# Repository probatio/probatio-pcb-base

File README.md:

# PCB for Support
A support is a part of probatio for expanding possible user's postures.

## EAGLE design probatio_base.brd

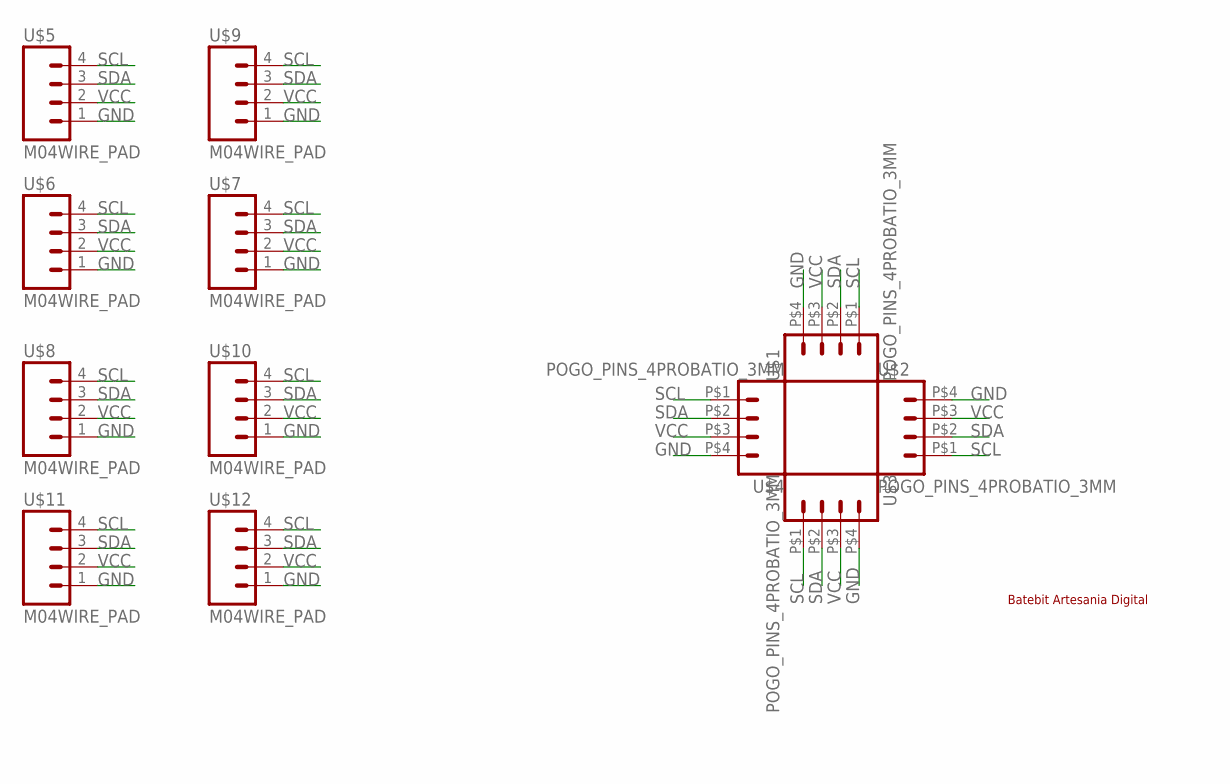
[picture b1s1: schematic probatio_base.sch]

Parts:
U$1, U$2, U$3, U$4: POGO_PINS_4PROBATIO_3MM; POGO-PINS-4
U$5, U$6, U$7, U$8, U$9, U$10, U$11, U$12: M04WIRE_PAD; 1X04_SMD
U$13: BATEBIT_PEQ

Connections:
GND: U$1.P$4 (4), U$2.P$4 (4), U$3.P$4 (4), U$4.P$4 (4), U$5.1, U$6.1, U$7.1, U$8.1, U$9.1, U$10.1, U$11.1, U$12.1
SCL: U$1.P$1 (1), U$2.P$1 (1), U$3.P$1 (1), U$4.P$1 (1), U$5.4, U$6.4, U$7.4, U$8.4, U$9.4, U$10.4, U$11.4, U$12.4
SDA: U$1.P$2 (2), U$2.P$2 (2), U$3.P$2 (2), U$4.P$2 (2), U$5.3, U$6.3, U$7.3, U$8.3, U$9.3, U$10.3, U$11.3, U$12.3
VCC: U$1.P$3 (3), U$2.P$3 (3), U$3.P$3 (3), U$4.P$3 (3), U$5.2, U$6.2, U$7.2, U$8.2, U$9.2, U$10.2, U$11.2, U$12.2

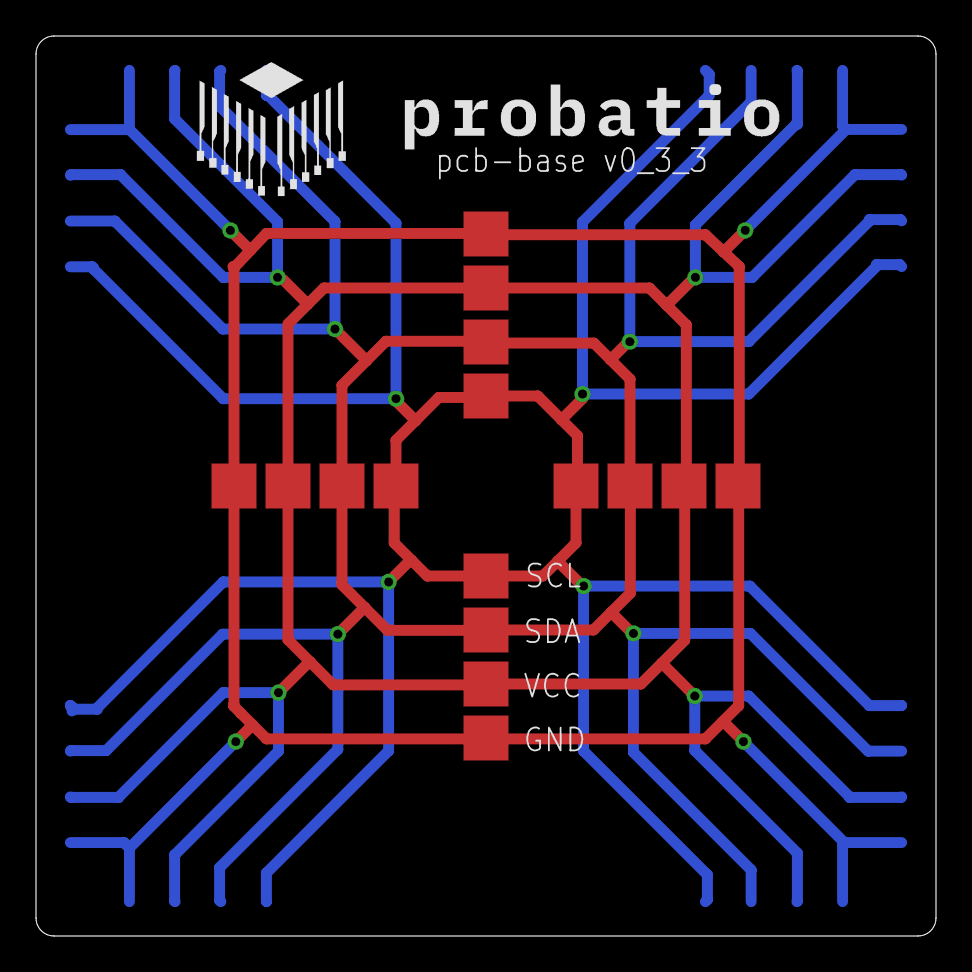
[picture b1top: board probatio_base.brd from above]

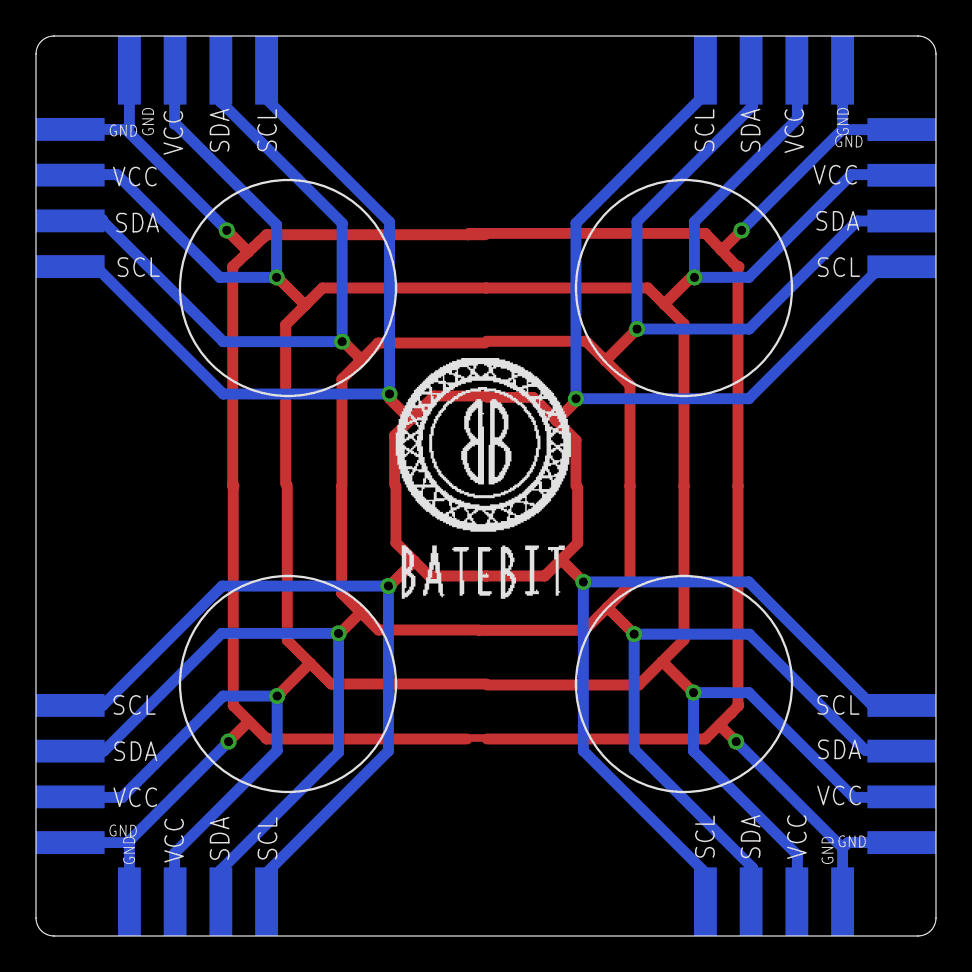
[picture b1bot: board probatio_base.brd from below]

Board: 2 copper layers, 50.0 x 50.0 mm, 14 parts (9 on the bottom side), 4 nets.

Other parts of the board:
U$14: PROBATIO

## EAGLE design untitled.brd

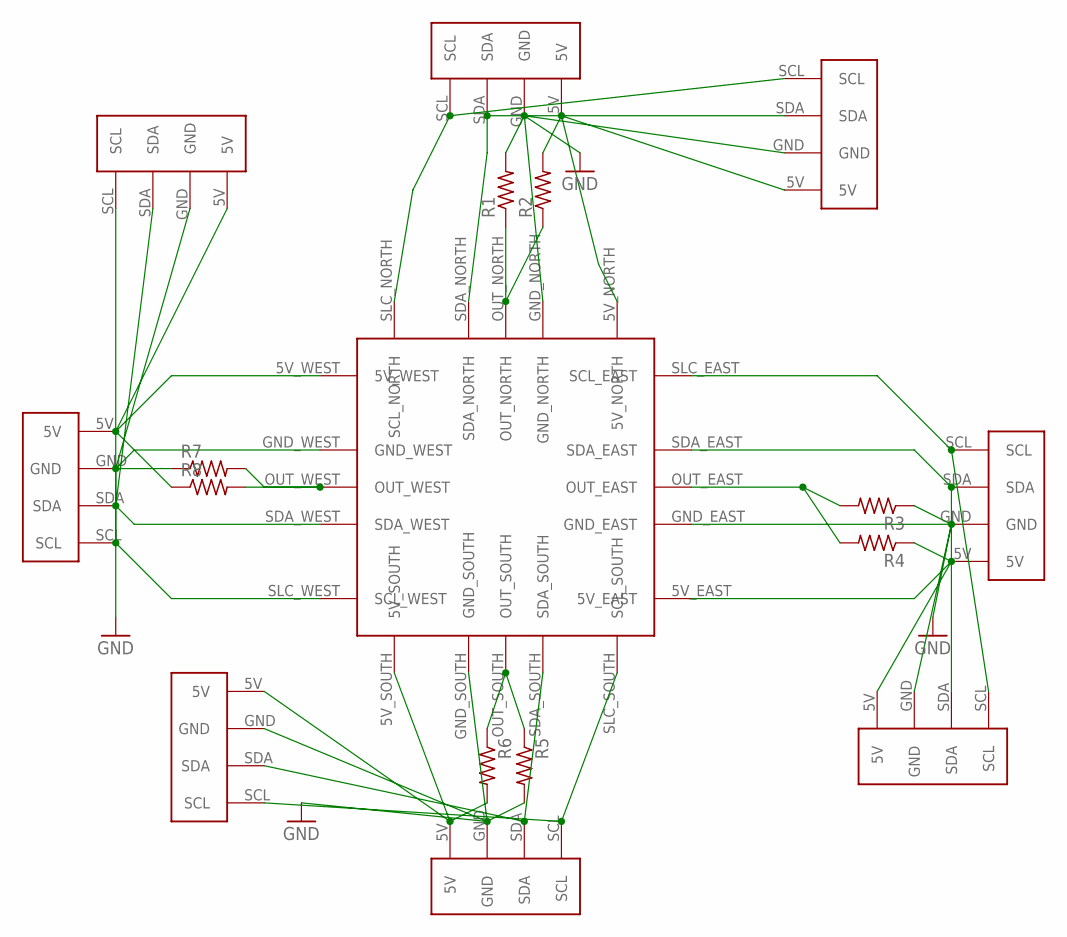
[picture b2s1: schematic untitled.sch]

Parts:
CENTER1: CONNECTORS_PIN_DEVICE; CONNECTORS_PIN
R1, R2, R3, R4, R5, R6, R7, R8: R-US_R0805; R0805
U$1, U$2, U$3, U$4, U$5, U$6, U$7, U$8: FOUR_SIDE_PINS

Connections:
GND: CENTER1.GND_EAST, CENTER1.GND_NORTH, CENTER1.GND_SOUTH, CENTER1.GND_WEST, R1.2, R3.1, R5.2, R7.1, U$1.GND, U$2.GND, U$3.GND, U$4.GND, U$5.GND, U$6.GND, U$7.GND, U$8.GND
unnamed: CENTER1.5V_EAST, R4.1, U$1.5V, U$6.5V
unnamed: CENTER1.OUT_EAST, R3.2, R4.2
unnamed: CENTER1.SDA_EAST, U$1.SDA, U$6.SDA
unnamed: CENTER1.SLC_EAST (SCL_EAST), U$1.SCL, U$6.SCL
unnamed: CENTER1.5V_NORTH, R2.2, U$2.5V, U$5.5V
unnamed: CENTER1.OUT_NORTH, R1.1, R2.1
unnamed: CENTER1.SDA_NORTH, U$2.SDA, U$5.SDA
unnamed: CENTER1.SLC_NORTH (SCL_NORTH), U$2.SCL, U$5.SCL
unnamed: CENTER1.5V_WEST, R8.1, U$3.5V, U$8.5V
unnamed: CENTER1.SDA_WEST, U$3.SDA, U$8.SDA
unnamed: CENTER1.SLC_WEST (SCL_WEST), U$3.SCL, U$8.SCL
unnamed: CENTER1.OUT_WEST, R7.2, R8.2
unnamed: CENTER1.5V_SOUTH, R6.2, U$4.5V, U$7.5V
unnamed: CENTER1.OUT_SOUTH, R5.1, R6.1
unnamed: CENTER1.SDA_SOUTH, U$4.SDA, U$7.SDA
unnamed: CENTER1.SLC_SOUTH (SCL_SOUTH), U$4.SCL, U$7.SCL

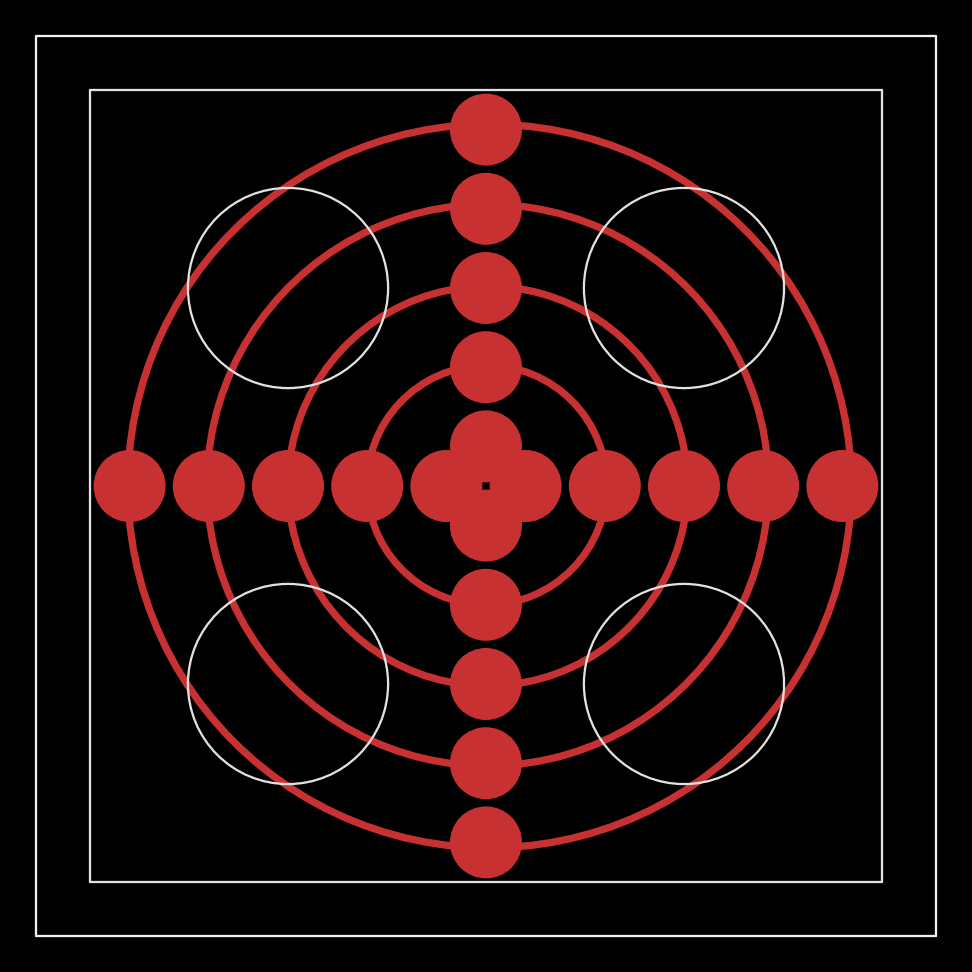
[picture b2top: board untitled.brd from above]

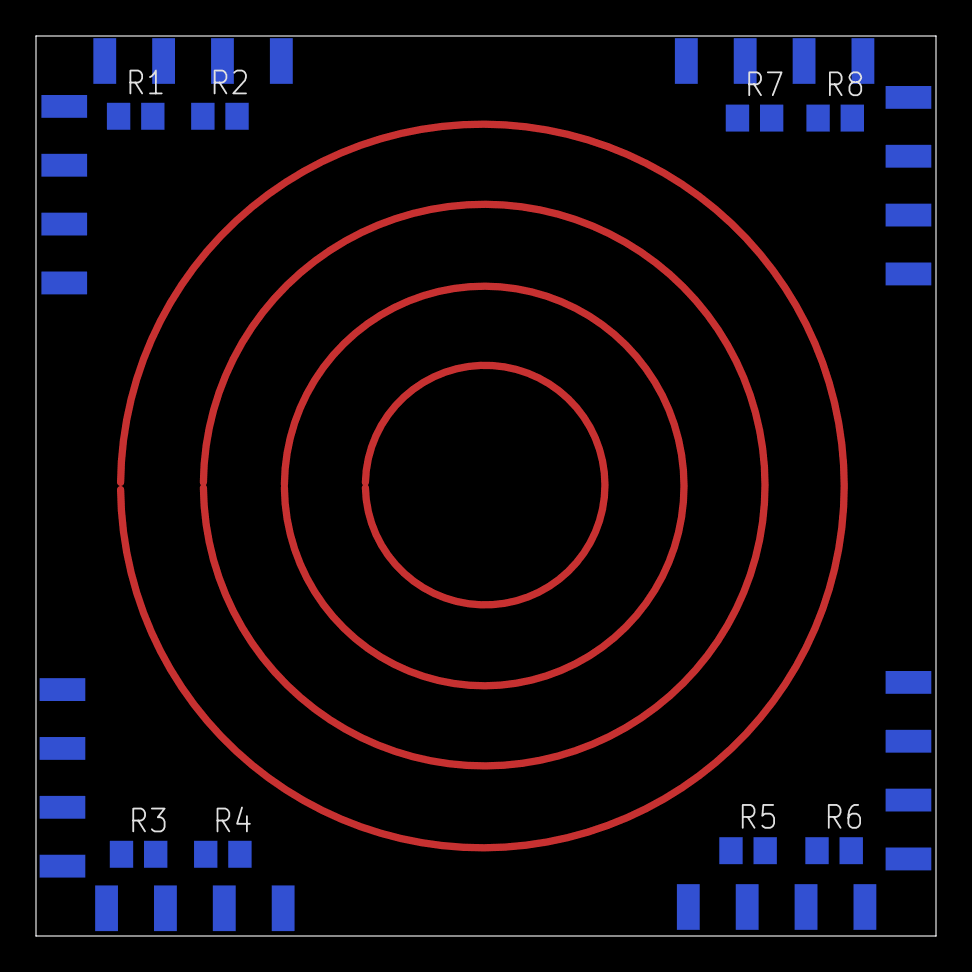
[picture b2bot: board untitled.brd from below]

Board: 2 copper layers, 50.0 x 50.0 mm, 17 parts (16 on the bottom side), 17 nets.

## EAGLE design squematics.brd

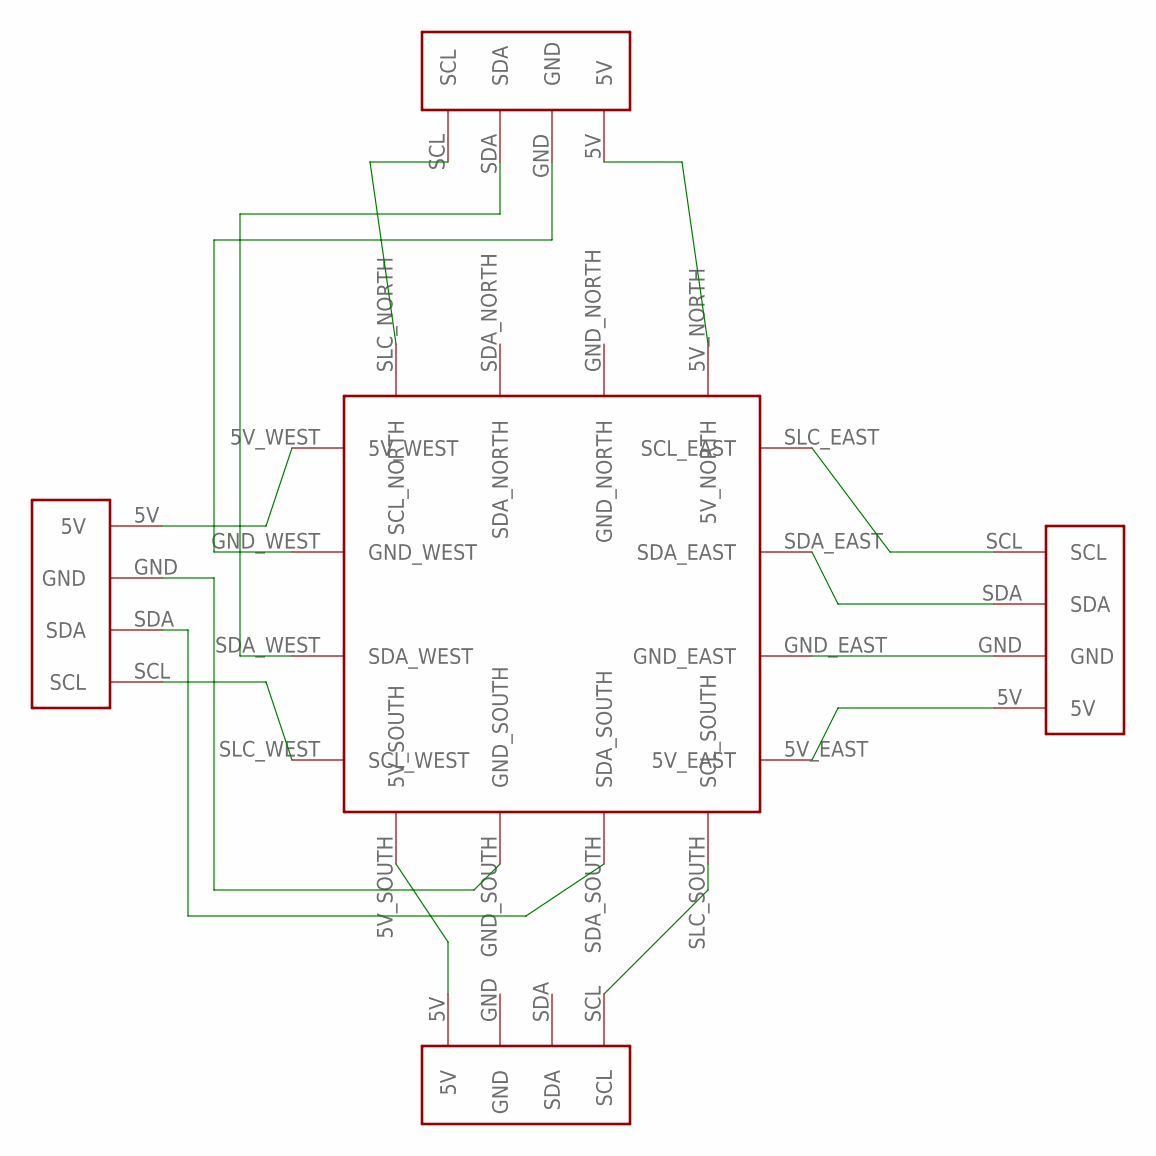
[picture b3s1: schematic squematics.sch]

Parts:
EAST: FOUR_SIDE_PINS
NORTH: FOUR_SIDE_PINS
U$1: CONNECTORS_PIN_DEVICE; CONNECTORS_PIN
U$2, U$3: FOUR_SIDE_PINS

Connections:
unnamed: NORTH.SCL, U$1.SLC_NORTH (SCL_NORTH)
unnamed: NORTH.SDA, U$1.SDA_WEST
unnamed: NORTH.GND, U$1.GND_WEST
unnamed: NORTH.5V, U$1.5V_NORTH
unnamed: EAST.SCL, U$1.SLC_EAST (SCL_EAST)
unnamed: EAST.SDA, U$1.SDA_EAST
unnamed: EAST.GND, U$1.GND_EAST
unnamed: EAST.5V, U$1.5V_EAST
unnamed: U$1.5V_WEST, U$2.5V
unnamed: U$1.SLC_WEST (SCL_WEST), U$2.SCL
unnamed: U$1.SDA_SOUTH, U$2.SDA
unnamed: U$1.GND_SOUTH, U$2.GND
unnamed: U$1.5V_SOUTH, U$3.5V
unnamed: U$1.SLC_SOUTH (SCL_SOUTH), U$3.SCL

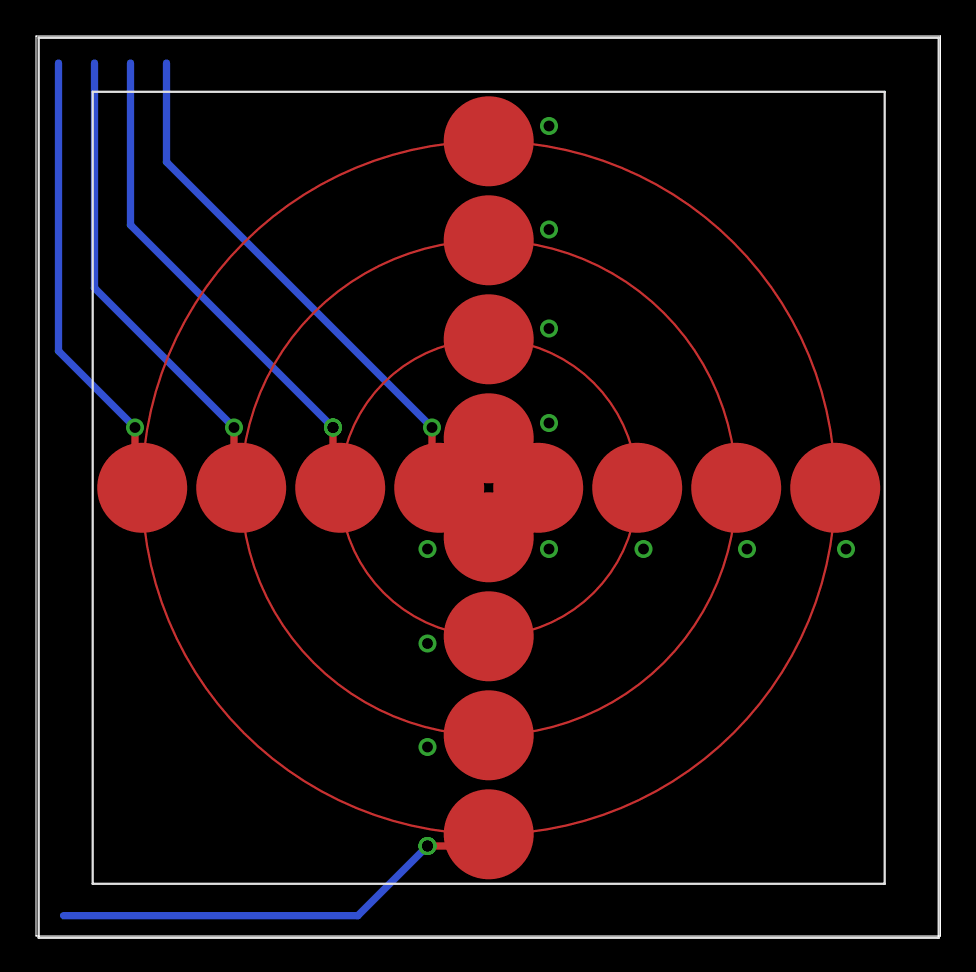
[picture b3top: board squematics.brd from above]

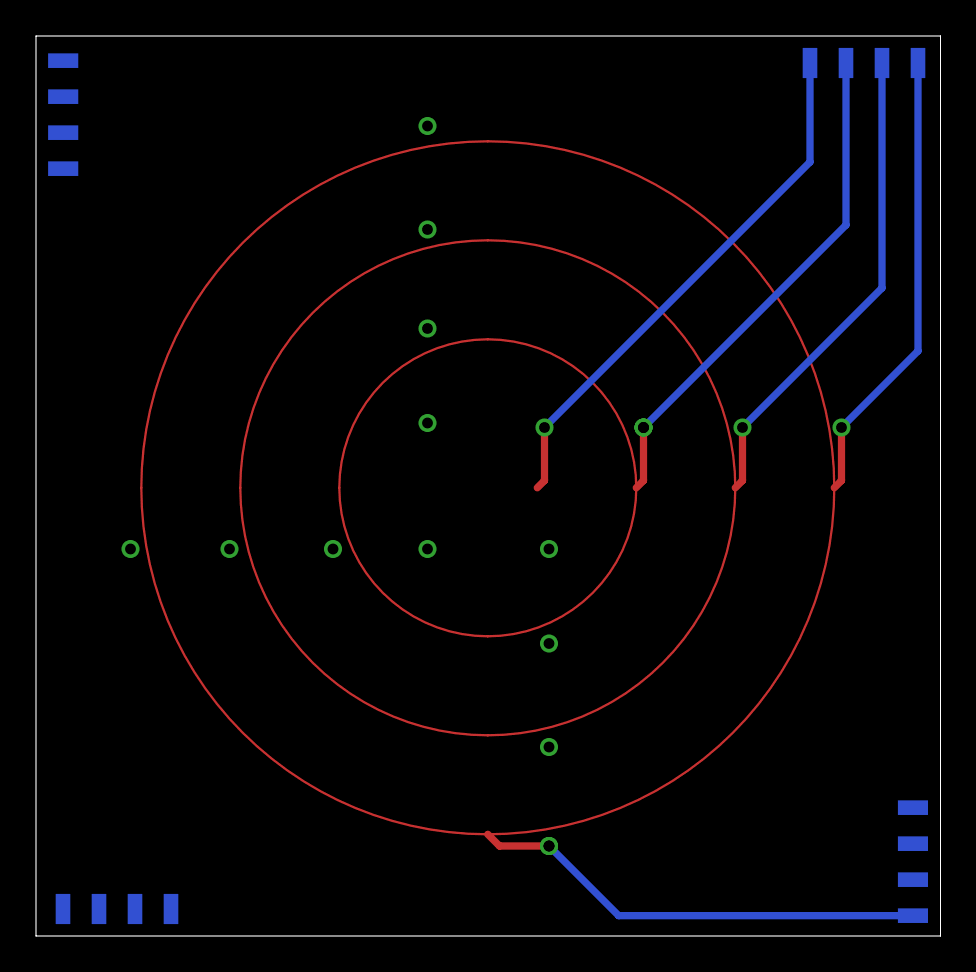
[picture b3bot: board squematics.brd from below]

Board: 2 copper layers, 50.2 x 50.0 mm, 5 parts (4 on the bottom side), 14 nets.

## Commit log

2019-08-09 Create LICENSE
2019-08-09 version 1.0
2019-08-09 version 2.0
2019-08-09 version 0.2.1
2019-08-10 CAD with new spacings
2019-08-10 new CAD version
2019-08-10 repository cleanup
2019-08-10 added batebit logo
2019-08-10 corrected magnet positions
2019-08-10 gerbers
2019-08-10 gerber zip
2019-08-10 label fix
2019-08-10 gerbers update
2019-08-28 Bug fix: changing layers of pads
2019-09-01 Update probatio_base.brd
    Last adjustments for 0.3.1
2019-09-01 Update probatio_base.brd
    Checking connections
2019-09-01 Gerbers generated
2019-09-11 Update LICENSE
2019-09-26 Renaming gerber zip to match version naming 0.3.1
2020-12-16 longer smd pads and no drills
2020-12-16 probatio logo
2020-12-31 Change from 'base-pcb' to 'pcb-base'
2021-02-25 longer pads

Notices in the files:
README.md:
License: CC BY-NC-SA 4.0
parts and their libraries:
SparkFun-Aesthetics: Licensing: Creative Commons ShareAlike 4.0 International - https://creativecommons.org/licenses/by-sa/4.0
